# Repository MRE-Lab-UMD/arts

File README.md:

# ARTS — Autonomous Robotic Translational System

An open-source, < $150,000, three-arm robotic laparoscopic platform for surgical-autonomy
research: teleoperation, imitation learning, and supervised autonomy. It is built from
universal robot arms, standard da Vinci instruments and open-source software (ROS 2 Jazzy,
ros2_control, pinocchio, proxsuite, Ruckig), plus the unavoidable OEM drivers. It is designed so
that a lab can buy the bill of materials, run one install script (or build the Docker images with
it) and reproduce the system; no outside lab has done a fresh install yet.

ARTS has two parts:
- **The system:** a patient cart with two tool arms and a camera arm, a surgeon console, and
  one control law for teleoperation, scripted pose commands and learned policies. It holds a
  remote center of motion (RCM) in software, records everything to MCAP, and checks collisions.
- **The tool module:** UR-to-da Vinci adapters that drive da Vinci X instruments (wrist, jaw,
  roll) through Dynamixel disc drives with automatic homing, plus energy through the ESU-TAP
  board (monopolar cut and coag, bipolar; by pedal or software, logged).

Rules, locked decisions and the status checklist are in [`AGENTS.md`](AGENTS.md); the reasoning
behind each decision is in [`docs/decisions/`](docs/decisions/).

---

## The system at a glance

| Station | What it holds |
|---|---|
| **Patient cart** | Vention pedestal; 2× UR5e tool arms (`psm_left`, `psm_right`, 500 Hz) with da Vinci X instruments on the ARTS adapters; 1× UR5 CB3 camera arm (`ecm`, 125 Hz) with a 12 mm stereo endoscope on two FLIR cameras, triggered by the ARTS sync box; trainer box; main PC; ARM HOLD relays |
| **Support tower** | Monitor 4 (tower view); ESU behind the ESU-TAP board; light source; smoke evacuator; irrigation and suction pumps |
| **Surgeon console** | 2× Haply Inverse3 + VerseGrip (`mtm_left`, `mtm_right`); GOOVIS stereo head-mounted display with head sensor; teleop footswitch (clutch, camera, record); ESU pedals |
| **Supervisor station** | Monitors 1–2, keyboard and mouse (the operator GUI and RViz); ARM HOLD button box |

**Control.** Every motion source sends the same message, a tool-tip pose target
(`<arm>/tool_tip_target`). Sources are the teleop follower, the camera control, the gamepad
jog, benchmark scripts and future policies. One controller per arm turns it into joint
commands: a resolved-rate law with the RCM as a hard constraint in a QP, then Ruckig for
jerk-limited smoothing, then UR `speedj` (`servoj` on the camera arm). Teleop and autonomy
differ only in the source.

**Safety.**
- ARM HOLD stops all three arms (UR safeguard stop, Category 2).
- The collision guard holds every arm when two capsules, between arms or within one arm, come
  closer than 20 mm.
- Each controller holds if its reference goes stale, the RCM breaks by more than 5 mm, or the
  instrument state goes stale.
- The teleop follower disengages on any of these and re-engages only on a fresh pedal press.

## Measured performance

All on the production workstation and the real arms. Full reports in
[`docs/benchmarks/`](docs/benchmarks/).

| What | Result |
|---|---|
| Real-time kernel latency under CPU + GPU load | 19 µs worst case |
| Servo loop, UR5e, 10 min | 499.994 Hz, jitter 3.8 % of the period, 0 missed cycles |
| Teleop motion-to-motion latency (120 fps video) | 58 ms |
| Glass-to-glass video latency | 67.8 ms |
| Stereo camera skew (hardware-triggered, PCB) | 2.8 ± 3.2 µs |
| Dual-camera recording, 30 min | 100 % of frames, 0 gaps |
| ARM HOLD stop at 20 mm/s | 1.46 mm |
| Pose repeatability (ISO 9283 RP, optical tracker, 5 poses × 30) | 0.14–0.25 mm per pose, 0 misses |
| RCM drift (optical tracker, 3 × 5 min) | pivot error 0.34–0.37 mm mean per trial, drift ≤ 0.01 mm/min |

---

## Install

```bash
git clone <repo-url> ~/arts && cd ~/arts
./arts_install.sh          # creates ~/arts_local/ (SDKs, third-party workspaces, builds); idempotent
source ~/arts/arts_ros2_ws/install/setup.bash     # the ONLY setup file you ever source to run
```

**Before installing, bring the ROS apt packages up to date** (`sudo apt update && sudo apt upgrade`).
ROS's apt repository is rolling and ARTS cannot pin it; older copies of `ros-jazzy-ur-msgs`,
`ros-jazzy-ur-client-library` and `ros-jazzy-generate-parameter-library(-py)` fail deep in the C++
build rather than at a prerequisite check (outside install, 2026-11-09; ARTS was built with 2.6.0,
2.15.2 and 0.7.6).

The repository holds only recipes, manifests and first-party source. Everything heavy
(> 100 GB) is built into `~/arts_local/`. Vendor-account SDKs, such as FLIR Spinnaker, are
downloaded by hand: the installer says what to download and where to put it.

**No stereo cameras (mock robot, simulation)?** Skip the FLIR SDK entirely:
`ARTS_ENABLE_FLIR=0 ./arts_install.sh`. With cameras, download Spinnaker 4.2.0.88 (Ubuntu 22.04,
amd64) from [Teledyne's Spinnaker page](https://www.teledynevisionsolutions.com/products/spinnaker-sdk/)
(free account; older releases under "All Versions") into `~/arts_local/oem_drivers/spinnaker-4.2.0.88/`.
If only a newer release is offered, extract it into `~/arts_local/oem_drivers/spinnaker-<version>/`
and run `ARTS_SPINNAKER_VERSION=<version> ./arts_install.sh`; the installer reports that this SDK
is not the one ARTS's camera results were measured with. Host setup
(RT kernel, NVIDIA driver, `isolcpus`, udev, DDS) is in
[`docs/host_prerequisites.md`](docs/host_prerequisites.md). The full host log and the
Docker images are in [`docs/host_setup_log.md`](docs/host_setup_log.md).

**Docker** (the same recipes, in containers; needs Docker with the NVIDIA container toolkit):
```bash
./arts_install.sh --path docker      # builds arts-base -> arts-flir -> arts:jazzy (FLIR SDK as for bare metal;
                                     # with ARTS_ENABLE_FLIR=0: arts-base -> arts:jazzy, no SDK)
docker compose -f deploy/docker/compose.yaml run --rm arts \
    src/arts_controllers/test/run_servo_smoke_test.sh                        # a mock arm moves
docker compose -f deploy/docker/compose.yaml run --rm arts \
    ros2 launch arts_driver arts_bringup.launch.py psm_left:=true psm_right:=true ecm:=true rviz:=true
```
The last line runs all three arms on mock hardware with RViz on your display. The smoke test
runs its own mock arm on its own ROS domain, so it does not move the arms in that RViz; add
`gamepad:=true` to the bringup to jog them. `compose.yaml` also has one service per hardware
module (`--profile patient-cart`, `--profile surgeon-console`). No image is published, so
every user builds them; the Docker path is tested on mock hardware only, not yet on the real arms.

**CAD meshes for RViz (optional, one time).** Without them RViz draws the pedestal as a grey
box and the arms without adapters; nothing else depends on them. The arm mounts never come
from a mesh: they are committed in `arts_description/config/mount_transforms.yaml`, so every
install places the arms identically. Meshes are generated into `~/arts_local/description_catalog/`
(never committed; Docker mounts that folder read-only):

1. **Pedestal (Vention's geometry, not redistributable, so you download it):** open the
   pedestal's Vention design page (the link in the pedestal row of
   [`docs/bom/bom.csv`](docs/bom/bom.csv)) → *Open in 3D* (free Vention account) →
   *Downloads* → *Download Assembly*, and save `VentionAssembly_<design>_v<N>.STEP` in
   `~/arts_local/description_catalog/parts/1_pedestal/0_incoming/`.
2. **Import** (pinned venv; the pedestal takes about 80 s and writes an ~80 MB mesh):
   ```bash
   cd ~/arts/arts_ros2_ws/src/arts_description/scripts
   python3 -m venv ~/arts_local/venvs/pedestal_import
   ~/arts_local/venvs/pedestal_import/bin/pip install -r requirements.txt
   PY=~/arts_local/venvs/pedestal_import/bin/python
   $PY -I import_pedestal_step.py ~/arts_local/description_catalog/parts/1_pedestal/0_incoming/VentionAssembly_*.STEP
   $PY -I import_tool_step.py adapter     ~/arts/hardware/tool_adapter/adapter_assembly.step
   $PY -I import_tool_step.py laparoscope ~/arts/hardware/laparoscope/laparoscope_assembly.step
   ```
   The pedestal import ends with a **mount check**: it compares where Vention's assembly puts
   the three arm bases with the committed mounts and prints `mount check PASSED`. If it fails
   (exit 2), your download is a different revision of the stand than ARTS's mounts were read
   from (v8); RViz would show the arms off the pedestal. Do not edit the mounts to match it;
   open an issue.
3. Restart the bringup: `cart_tf` logs `pedestal: Vention mesh ...` and RViz shows the real cart.

**One sourcing rule.** To run, source `~/arts/arts_ros2_ws/install/setup.bash` and nothing
else; it chains down to ROS 2. Builds always run in a clean `env -i` shell
(`./arts_install.sh --arts-only` rebuilds the ARTS workspace).

---

## Running a session

Every session follows the same order. Steps marked **(go)** move hardware: one person holds the
pendant and the e-stop and gives the go.

All terminals start with:
```bash
source /etc/profile.d/arts-dds.sh; source ~/arts/arts_ros2_ws/install/setup.bash
B=~/arts/arts_ros2_ws/src/arts_controllers/bench
```

### 1. Power and pendants
Power on the three arms and release the brakes. **Do not press Play yet.** Check the monitor
layout with `xrandr --listmonitors`: the tower display at `0,0`, the GOOVIS at `1920,0`.

### 2. Instrument start (every session, for every instrument)

An instrument is homed and zeroed at the start of every session, never just re-zeroed:
instrument state can change between sessions.

1. **Instrument OFF the adapter.** Start the homing (profiles: `forceps` for the ProGrasp and
   the bipolar forceps, `needledriver`, `hook`, `scissors`):
   ```bash
   ros2 launch arts_dv_tool_driver tool_homing.launch.py arm:=psm_left tool:=forceps
   ```
   Wait for "Start positions reached". A warning that a motor missed its start means the
   instrument was on: take it off and restart.
2. **Instrument ON, press A** on the gamepad. Wait for "All homing complete" (~30 s), then Ctrl+C.
3. **Visual zero**, with the disc drives only (no arm running):
   ```bash
   ros2 launch arts_driver arts_bringup.launch.py psm_left_tool:=prograsp_forceps psm_left_tool_actuator:=true \
       psm_right_tool:=large_needle_driver psm_right_tool_actuator:=true gamepad:=true allow_mode_write:=true use_fake_hardware:=false
   ```
   Select the arm with the gamepad (**Back** = psm_left, **Start** = psm_right). Hold **LB**
   and press **B** for joint mode, then straighten the wrist with the jaws just closed. If the
   jaws are off, use disc mode (**LB + A**) for them. Set the zero with **LB + X**, then Ctrl+C.

Instrument names (`psm_*_tool:=`): `prograsp_forceps`, `large_needle_driver`,
`bipolar_fenestrated_forceps`, `permanent_cautery_hook`, `monopolar_curved_scissors`.

### 3. Bring up the system

**With the operator GUI** (supervisor station):
```bash
ros2 run arts_gui arts_gui.py
```
- **Modules tab:** pick each PSM's instrument, then start the arms, their disc drives, the
  cameras, MTMs, footswitch, head sensor and ESU. Presets start common sets.
- The GUI starts one cart frame publisher and one collision guard for all arms. Each module's
  log shows the exact terminal command, so any run can be reproduced.
- **Displays tab:** places the GOOVIS and tower views and opens RViz, configured for the
  running arms.
- **Surgery mode tab:** turns each arm's RCM on or off, and enables or disables software energy.

**Or from one terminal** (the same switches):
```bash
ros2 launch arts_driver arts_bringup.launch.py \
    psm_left:=true psm_left_tool:=prograsp_forceps psm_left_tool_actuator:=true \
    psm_right:=true psm_right_tool:=large_needle_driver psm_right_tool_actuator:=true wrist:=true \
    ecm:=true ecm_stereo:=true ecm_stereo_sync:=true head_sensor:=true gamepad:=true \
    display:=true display_fullscreen:=true display_hmd_pos:=1920,0 display_tower_pos:=0,0 \
    image_bag:=$HOME/arts_local/<session_name>/images image_bag_paused:=true \
    rviz:=true use_fake_hardware:=false
```
`image_bag:=` records the stereo video: both cameras at 1536×1024 raw Bayer, 30 Hz, in the
camera process beside the display (decision 5). With `image_bag_paused:=true` nothing is written
until the **record pedal** (right) starts an episode, and its next press ends it; the marks are
on `/console/episode_mark` (the footswitch runs in the teleop step below). Both cameras write
about **5.7 GB per minute**, so check the free space first and export after each session
(step 6). Keep `ecm_stereo_sync:=true` whenever the cameras run: without the sync box's agent the
box reboots about every 12 s and stops triggering for about 175 ms each time.

Then press **Play** on every pendant **(go)**. In RViz the collision capsules are green, yellow
below 50 mm, and red below 20 mm (every arm holds).

### 4. RCM on (minimally invasive mode)

**Through a port (trainer box or cannula).** With the RCM off, jog each instrument through its
port with the gamepad (hold **RB**) until the shaft crosses the port. Then put the RCM point at
the port, `d` metres back along the shaft:
```bash
python3 $B/set_rcm.py on --arm psm_left  --depth <d>
python3 $B/set_rcm.py on --arm psm_right --depth <d>
python3 $B/set_rcm.py on --arm ecm       --depth <d>
```
`d` is measured from a different point on each kind of arm:
- **PSM:** from the instrument's **wrist pitch axis** (the first wrist joint, where the shaft
  ends) back to the port. This holds with `wrist:=true`; without it, measure from the wrist yaw
  axis, 9 mm further out.
- **ECM:** from the **scope's distal tip** back to the port.

Tape marks every 10 mm on each shaft, counted from the wrist (or from the scope tip), let you
read `d` at the port. `set_rcm.py` refuses an RCM that leaves less than 5 mm of insertion.
Check with `set_rcm.py status --arm <arm>`, which prints the deviation and the insertion depth.
Seat cannulas in compliant ports, not rigid clamps: the point is placed by eye, so it can be a
few millimetres off the port's true pivot.

**Without a port** (free air), `on` alone uses the current shaft at the last depth (100 mm
before the first); for the ECM, `--depth 0.05`.

In the GUI, the Surgery mode tab switches the RCM on at the current shaft.

### 5. Teleoperate (go)
```bash
ARTS_TOOL=470093_prograsp_forceps.yaml ARTS_RIGHT_TOOL=471006_large_needle_driver.yaml ARTS_CAMERA=1 \
    ARTS_CAMERA_ARGS="-p camera_max_offset:=0.02" \
    ~/arts/arts_ros2_ws/src/arts_utilities/arts_teleop/test/run_teleop_real.sh ~/arts_local/<session_name> 20
```
This starts the MTM bridge, footswitch, both tool followers, the jaw followers and the camera
control, and records everything (state bag) for the given number of minutes.
- **Head in the GOOVIS** enables. Hold the **clutch pedal** to drive the tools.
- Hold the **middle pedal** to drive the camera with both hands (pan, zoom, steering-wheel
  roll); the tools disengage meanwhile.
- After a camera move, the tools re-engage through a 10° alignment gate.

The `ARTS_TOOL` file names are in `arts_dv_tool_driver/config/instruments/`. Energy:
`ARTS_ESU=1`.

### 6. Shut down
Ctrl+C the teleop, then **stop the pendant programs**, then Ctrl+C the bringup (this closes the
image bag). Then copy the session to an external disk, checked by hash; `--delete` removes the
local copy only if every hash matches:
```bash
~/arts/arts_ros2_ws/src/arts_utilities/arts_record/scripts/export_bag.sh \
    ~/arts_local/<session_name> /media/$USER/<disk>/ [--delete]
```

### Gamepad (Xbox)

| Input | Action |
|---|---|
| Back / Start / Guide | select psm_left / psm_right / ecm |
| hold **RB** | arm jog (deadman). RCM off: left stick = tip sideways, LT/RT = in/out along the shaft, right stick X = roll, right stick Y = pitch, d-pad left/right = yaw. RCM on: left stick = pivot about the RCM, LT/RT = insert/retract |
| hold **LB** | instrument jog, refused while the arm's controller runs. A = disc mode, B = joint mode (left stick X roll, right stick X pitch, d-pad yaw, **RT opens the jaw**), **X = set the zero** |

### Collision guard

The guard is on by default with any arm. Arm links are capsules fitted at start-up to the
vendor collision meshes (one per link, end spheres centred on the joint housings); the adapters,
the first 150 mm of each instrument shaft, the endoscope camera head and the first 200 mm of the
scope are capsules from their CAD; the pedestal is three 22 cm spheres where the arms are held
(between each tool-arm mount and the camera-arm mount, and between the tool-arm mounts).

When it holds:
- every arm holds position, and the followers disengage;
- `/collision_guard/state` names the pair;
- release, then separate the arms:
  ```bash
  ros2 service call /collision_guard/release std_srvs/srv/Trigger
  ```
  After the release, motion that separates the pair is free. Moving closer holds again.

---

## Experiments

| Experiment | Instruments | How |
|---|---|---|
| FLS peg transfer (3 triangles left → right, 3 right → left, mid-air handoff) | 2× large needle driver | RCM on through the trainer box ports. Time, triangles moved, drops, failed handoffs; the bags give path length, engagements and RCM deviation: [`docs/modules/bench_session_20261109.md`](docs/modules/bench_session_20261109.md) |
| Intracorporeal suturing + knot on a silicone pad | 2× large needle driver | Same setup; time, knot security, distance from the marked points |
| Porcine cholecystectomy subtask: blunt dissection + monopolar cut | right hook, left bipolar forceps | `ARTS_ESU=1`; energy by pedal or the GUI's Energy box (logged on `/esu/state`) |
| Porcine spleen: suction + spray coag; bipolar coag | right hook, left bipolar forceps (+ suction tool) | Same, ESU mode set on the generator |
| Pose repeatability, RCM drift (optical tracker) | ProGrasp + tracker markers | [`docs/modules/bench_session_20261107.md`](docs/modules/bench_session_20261107.md) |

Mock hardware: any bringup with `use_fake_hardware:=true` (the default) runs without the arms.
The regression tests run on mock through `arts_controllers/test/run_servo_smoke_test.sh <test>`.

---

## Repository

| Path | Contents |
|---|---|
| `arts_ros2_ws/src/arts_driver` | bringup launch (one switch per module), arm launch, configs (arms, instruments, tool tips) |
| `arts_ros2_ws/src/arts_controllers` | the servo controller (resolved-rate law, RCM QP, wrist), bench scripts, mock tests |
| `arts_ros2_ws/src/arts_embedded` | `arts_dv_tool_driver` (disc drive, homing), `arts_esu` (ESU-TAP), `arts_camera_sync` (sync box firmware + PCB) |
| `arts_ros2_ws/src/arts_utilities` | `arts_teleop` (followers, camera control, gamepad, footswitch), `arts_safety` (collision guard), `arts_gui`, `arts_record`, `arts_display`, `arts_kinematics`, `arts_datasets` |
| `arts_ros2_ws/src/arts_description` | URDF/xacro for the cart, arms, adapters and endoscope; RViz configs |
| `middle_overlay_ros2_wss/`, `open_source_software/`, `oem_drivers/` | pinned manifests and recipes for everything third-party (built into `~/arts_local/`) |
| `deploy/` | install modules (bare metal and Docker share them), host setup, benchmarks, CI |
| `hardware/` | adapter and endoscope mechanical designs |
| `docs/` | decisions, module docs, bench procedures, benchmark reports, BOM |

Every dependency is pinned (tag or commit, `=version`, `==version`); see
[`docs/dependency_pinning.md`](docs/dependency_pinning.md). Layout details:
[`docs/repo_layout.md`](docs/repo_layout.md). License: Apache-2.0.

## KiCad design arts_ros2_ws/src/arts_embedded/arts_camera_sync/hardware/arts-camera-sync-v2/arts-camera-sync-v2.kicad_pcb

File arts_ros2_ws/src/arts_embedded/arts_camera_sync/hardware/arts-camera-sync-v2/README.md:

# arts-camera-sync-v2

First published revision of the ARTS camera sync box.

| | |
|---|---|
| **Status** | Layout approved 2026-09-08. KiCad 9 source is in this directory. JLCPCB order queued (2 layer, 1.6 mm, HASL lead-free, green; PCBA R1–R6 + D1–D6 only). Not yet purchased or fabricated. No committed skew baseline. |
| **Toolchain** | KiCad 9 |
| **Fab house / options** | JLCPCB — order queued, awaiting purchase. 2 layer, 1.6 mm, HASL lead-free, green. Assembly: R1–R6 (0402) and D1–D6 (SOD-323) only. Sockets, Phoenix J1–J3, DevKitC, JP1 hand-fit. |
| **Known-good firmware** | none on this board yet. The breadboard rig ran `arts_camera_sync` firmware as of 2026-08-19 (micro-ROS build, 266 KB); this board must be re-baselined against whatever revision is current when it is populated. |
| **Supersedes** | the breadboard + OONO screw-terminal rig described in `docs/modules/camera_sync_wiring.md` |

Open `arts-camera-sync-v2.kicad_pro`. Libraries resolve through `${KIPRJMOD}`.

## What this board is for

It fires all cameras from one hardware edge and captures each camera's `ExposureActive`
strobe back on one 80 MHz counter, so L/R stereo skew is a hardware measurement — the
difference between two capture timestamps on a single counter, independent of ROS,
Spinnaker, DDS and any clock estimator.

The electrical function is small: three series resistors, three pull-ups, three connectors
and a socketed ESP32. The board exists not because the circuit is complex but because a
spring-clip contact on stranded wire fails intermittently, and intermittently here means a
dropped strobe on some pulses with a plausible skew computed from the rest — a silently
wrong number, which is the exact failure this box was built to eliminate.

## What it must beat

The breadboard rig measured skew mean 3.52 µs / max 10.44 µs with a **2.81 µs systematic**
offset, of which 0.72 µs was attributable to the strobe-side rise-delay mismatch and the
remaining ~1.9 µs to something upstream — 560 Ω tolerance changing the optocoupler drive
current, cable length, or camera-internal variation. The single highest-value change on this
board is therefore **1 % resistors from one reel instead of 5 % carbon films**, which
addresses the largest identified contributor for a few cents. See `02_bom.md`.

**No committed skew baseline may come from the breadboard.** Resistor instances, lead lengths
and contact resistance move the systematic term by the same order as the effect being
measured, so the breadboard number is a bring-up result and the board's number is the
published one.

## Contents

```
arts-camera-sync-v2.kicad_pro / .kicad_sch / .kicad_pcb
fp-lib-table  sym-lib-table
libraries/                    project-local, ${KIPRJMOD}
design_package/
├─ 01_schematic_and_connections.md
├─ 02_bom.md
├─ 03_layout_and_fab.md
└─ 04_test_procedure.md
```

`production/` is absent until a fabricated revision exists. Read `01` first.

## Third-party EDA assets

| Asset | Source | Downloaded | License |
|---|---|---|---|
| `ESP32-DEVKITC-32E` symbol, footprint, STEP (`--3DModel-STEP-269445`) | [SnapEDA / Espressif ESP32-DEVKITC-32E](https://www.snapeda.com/parts/ESP32-DEVKITC-32E/Espressif+Systems/view-part/) | 2026-08-19 | SnapEDA standard: CC-BY-SA 4.0 with the SnapEDA Design Exception (permits use in a design without share-alike on the board). Re-verify at next download. |

Attribution to SnapEDA identifies nobody. Do not copy this part from another project's tree;
the fetch recipe is the URL above.

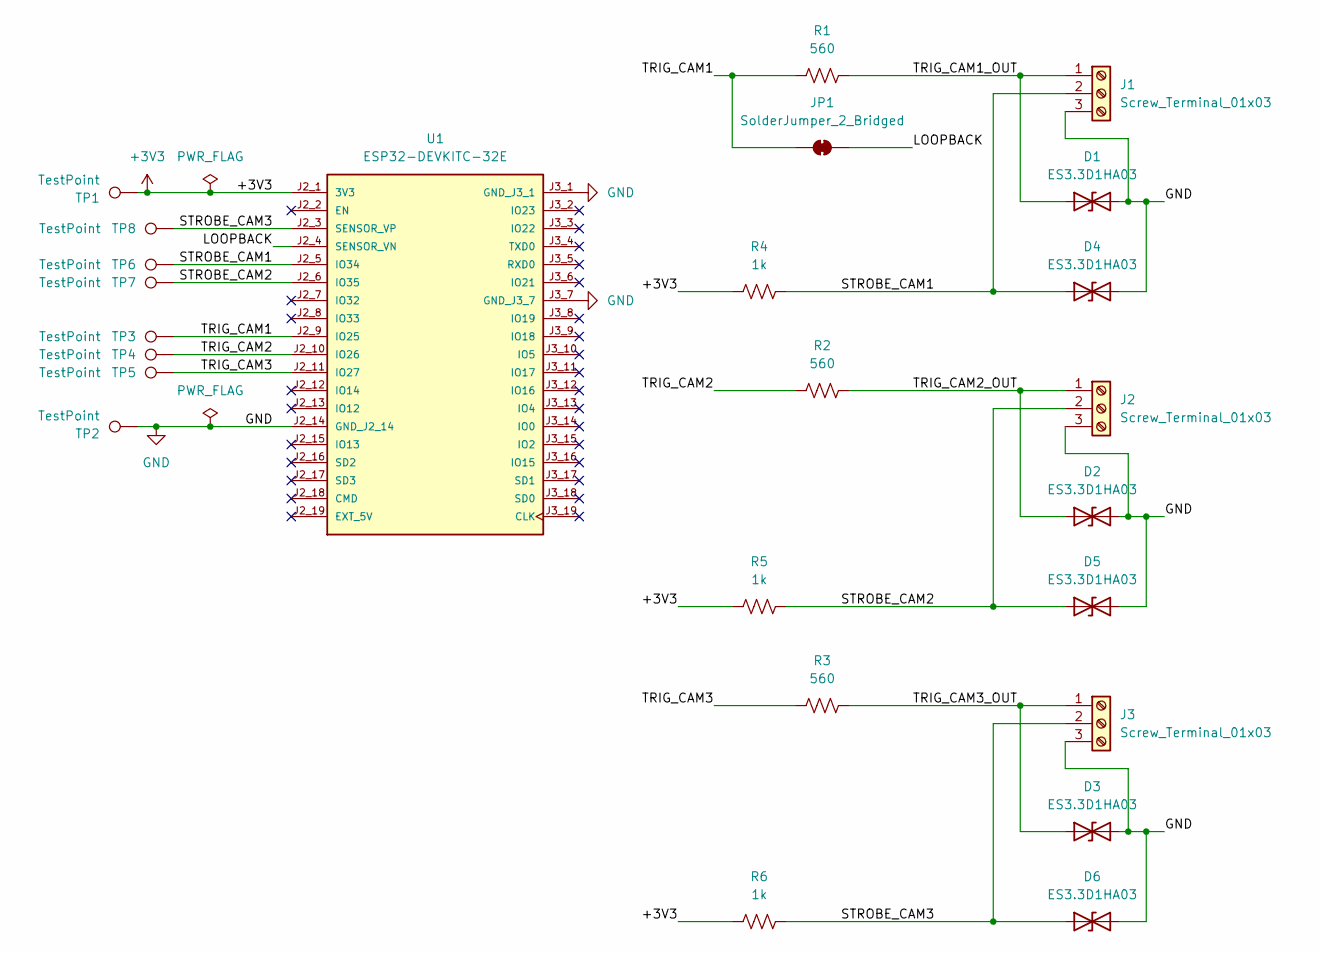
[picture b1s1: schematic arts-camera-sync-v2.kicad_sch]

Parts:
D1, D2, D3, D4, D5, D6: ES3.3D1HA03; D_SOD-323
J1, J2, J3: Screw_Terminal_01x03; TerminalBlock_Phoenix_MKDS-1,5-3-5.08_1x03_P5.08mm_Horizont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
JP1: SolderJumper_2_Bridged; SolderJumper-2_P1.3mm_Bridged_RoundedPad1.0x1.5mm
R1, R2, R3: 560; R_0402_1005Metric
R4, R5, R6: 1k; R_0402_1005Metric
TP1, TP2, TP3, TP4, TP5, TP6, TP7, TP8: TestPoint; TestPoint_Pad_D1.0mm
U1: ESP32-DEVKITC-32E; MODULE_ESP32-DEVKITC-32E; PARTREV 1.4

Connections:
+3V3: R4.1, R5.1, R6.1, TP1.1, U1.J2_1 (3V3)
/LOOPBACK: JP1.2 (B), U1.J2_4 (SENSOR_VN)
/STROBE_CAM1: D4.1 (A1), J1.2, R4.2, TP6.1, U1.J2_5 (IO34)
/STROBE_CAM2: D5.1 (A1), J2.2, R5.2, TP7.1, U1.J2_6 (IO35)
/STROBE_CAM3: D6.1 (A1), J3.2, R6.2, TP8.1, U1.J2_3 (SENSOR_VP)
/TRIG_CAM1: JP1.1 (A), R1.1, TP3.1, U1.J2_9 (IO25)
/TRIG_CAM1_OUT: D1.1 (A1), J1.1, R1.2
/TRIG_CAM2: R2.1, TP4.1, U1.J2_10 (IO26)
/TRIG_CAM2_OUT: D2.1 (A1), J2.1, R2.2
/TRIG_CAM3: R3.1, TP5.1, U1.J2_11 (IO27)
/TRIG_CAM3_OUT: D3.1 (A1), J3.1, R3.2
GND: D1.2 (A2), D2.2 (A2), D3.2 (A2), D4.2 (A2), D5.2 (A2), D6.2 (A2), J1.3, J2.3, J3.3, TP2.1, U1.J2_14 (GND_J2_14), U1.J3_1 (GND_J3_1), U1.J3_7 (GND_J3_7)

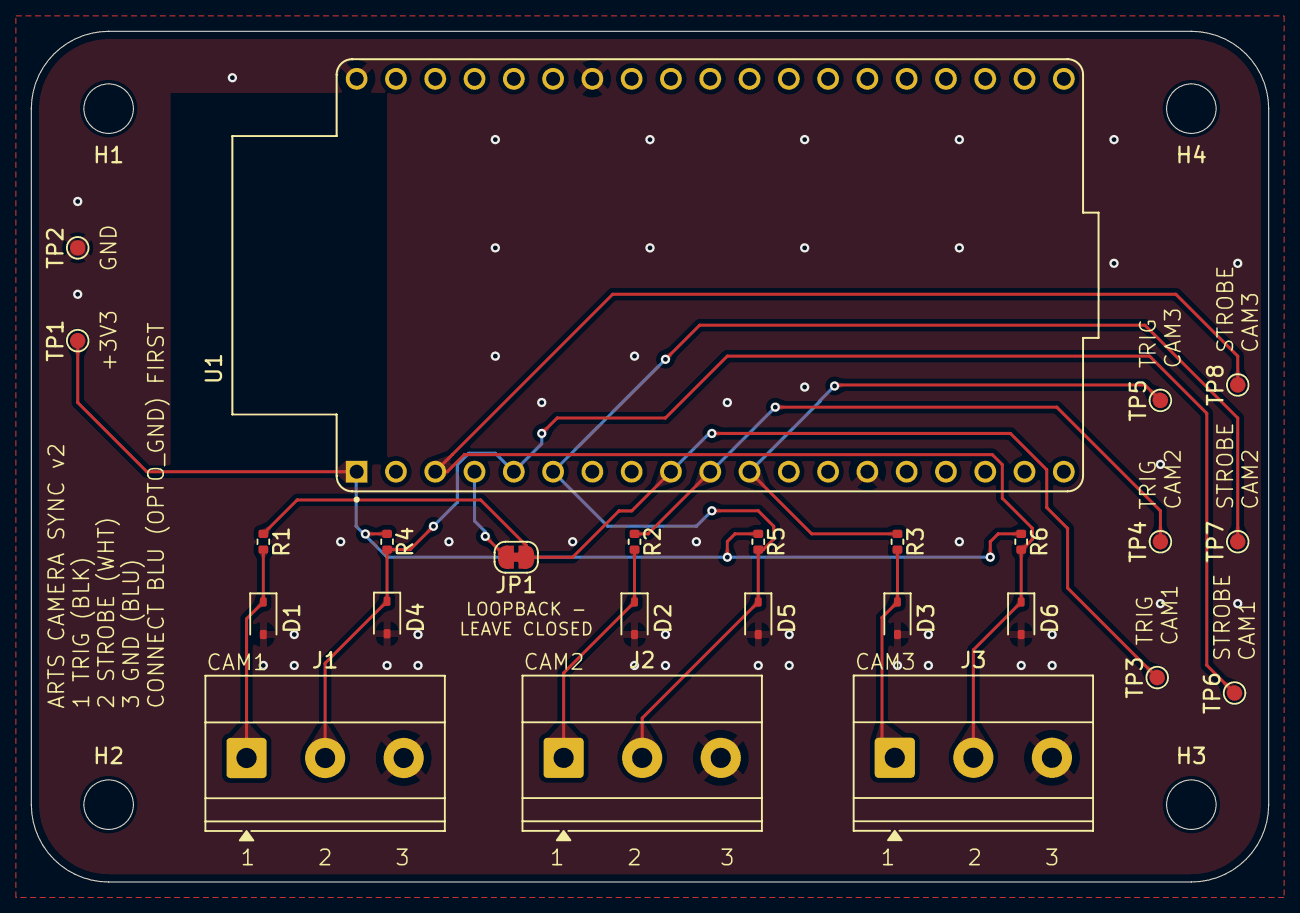
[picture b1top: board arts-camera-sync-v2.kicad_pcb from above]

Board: 2 copper layers, 80.0 x 55.0 mm, 29 parts (0 on the bottom side), 12 nets.

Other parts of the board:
H1, H2, H3, H4: MountingHole_3.2mm_M3_DIN965_Pad; MountingHole_3.2mm_M3
